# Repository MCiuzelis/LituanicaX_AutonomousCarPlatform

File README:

To activate the virtual env:
source ~/arducam_venv/bin/activate

hardware pwm:
sudo nano /boot/firmware/config.txt
dtoverlay=pwm-2chan,pin=12,func=4,pin2=18,func2=4

something similar for cam

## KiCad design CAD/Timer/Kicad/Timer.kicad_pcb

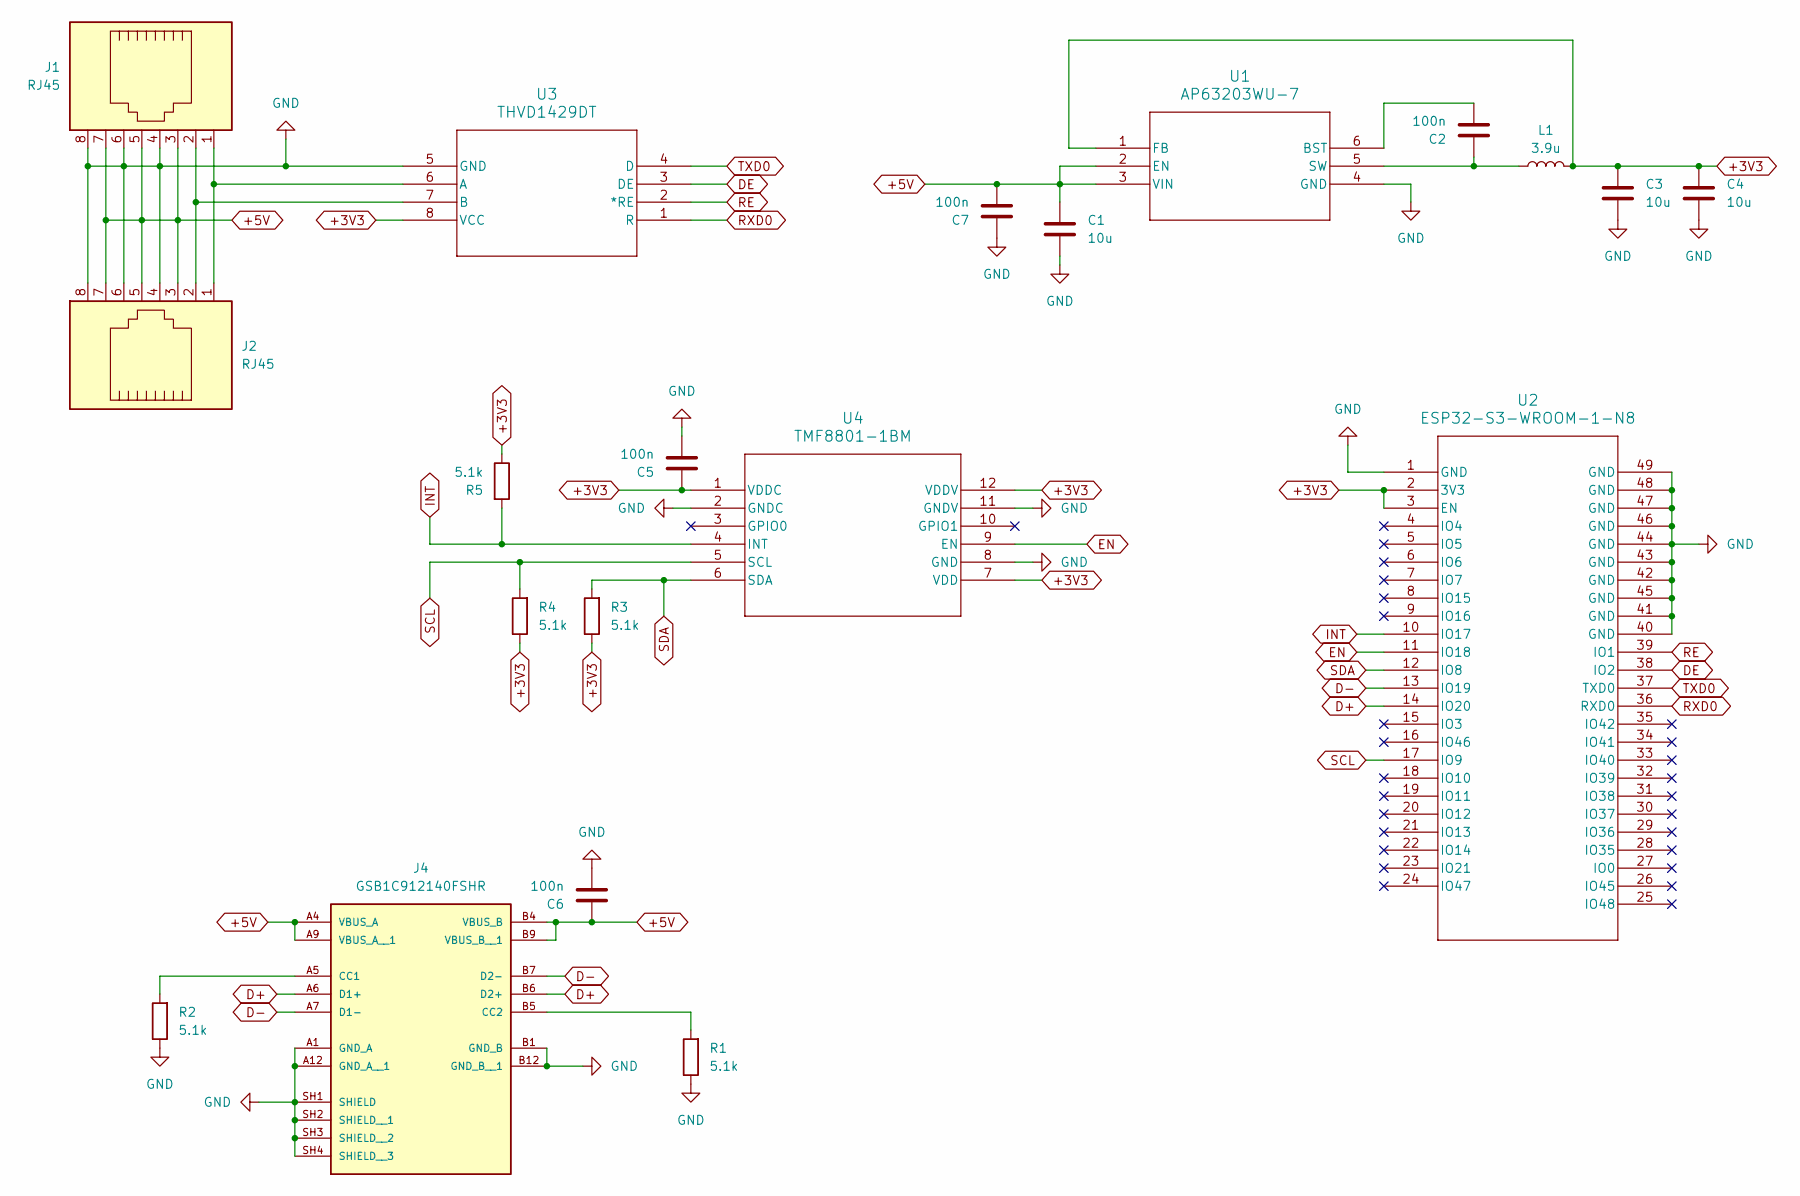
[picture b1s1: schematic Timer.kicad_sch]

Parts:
C1, C3, C4: 10u; C_1210_3225Metric_Pad1.33x2.70mm_HandSolder
C2, C5, C6, C7: 100n; C_0805_2012Metric_Pad1.18x1.45mm_HandSolder
J1, J2: RJ45; RJ45_Amphenol_RJHSE538X
J4: GSB1C912140FSHR; AMPHENOL_GSB1C912140FSHR; PARTREV AX1
L1: 3.9u; L_1210_3225Metric_Pad1.42x2.65mm_HandSolder
R1, R2, R3, R4, R5: 5.1k; R_0805_2012Metric_Pad1.20x1.40mm_HandSolder
U1: AP63203WU-7; AP63203WU-7_DIO
U2: ESP32-S3-WROOM-1-N8; ESP32-S3-WROOM-1_EXP
U3: THVD1429DT; D8_TEX
U4: TMF8801-1BM; TMF8801-1BM_AMS

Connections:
+3V3: C3.1, C4.1, C5.1, L1.2, R3.1, R4.1, R5.1, U1.1 (FB), U2.2 (3V3), U2.3 (EN), U3.8 (VCC), U4.1 (VDDC), U4.7 (VDD), U4.12 (VDDV)
+5V: C1.1, C6.1, C7.2, J1.3, J1.5, J1.7, J2.3, J2.5, J2.7, J4.A4 (VBUS_A), J4.A9 (VBUS_A__1), J4.B4 (VBUS_B), J4.B9 (VBUS_B__1), U1.2 (EN), U1.3 (VIN)
D+: J4.A6 (D1+), J4.B6 (D2+), U2.14 (IO20)
D-: J4.A7 (D1-), J4.B7 (D2-), U2.13 (IO19)
DE: U2.38 (IO2), U3.3 (DE)
EN: U2.11 (IO18), U4.9 (EN)
GND: C1.2, C3.2, C4.2, C5.2, C6.2, C7.1, J1.4, J1.6, J1.8, J2.4, J2.6, J2.8, J4.A1 (GND_A), J4.A12 (GND_A__1), J4.B1 (GND_B), J4.B12 (GND_B__1), J4.SH1 (SHIELD), J4.SH2 (SHIELD__1), J4.SH3 (SHIELD__2), J4.SH4 (SHIELD__3), R1.1, R2.1, U1.4 (GND), U2.1 (GND), U2.40 (GND), U2.41 (GND), U2.42 (GND), U2.43 (GND), U2.44 (GND), U2.45 (GND), U2.46 (GND), U2.47 (GND), U2.48 (GND), U2.49 (GND), U3.5 (GND), U4.2 (GNDC), U4.8 (GND), U4.11 (GNDV)
INT: R5.2, U2.10 (IO17), U4.4 (INT)
unnamed: J4.A5 (CC1), R2.2
unnamed: J4.B5 (CC2), R1.2
unnamed: C2.2, U1.6 (BST)
unnamed: C2.1, L1.1, U1.5 (SW)
unnamed: J1.1, J2.1, U3.6 (A)
unnamed: J1.2, J2.2, U3.7 (B)
RE: U2.39 (IO1), U3.2 (*RE)
RXD0: U2.36 (RXD0), U3.1 (R)
SCL: R4.2, U2.17 (IO9), U4.5 (SCL)
SDA: R3.2, U2.12 (IO8), U4.6 (SDA)
TXD0: U2.37 (TXD0), U3.4 (D)

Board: 2 copper layers, 20 parts (1 on the bottom side), 19 nets, no tracks yet.

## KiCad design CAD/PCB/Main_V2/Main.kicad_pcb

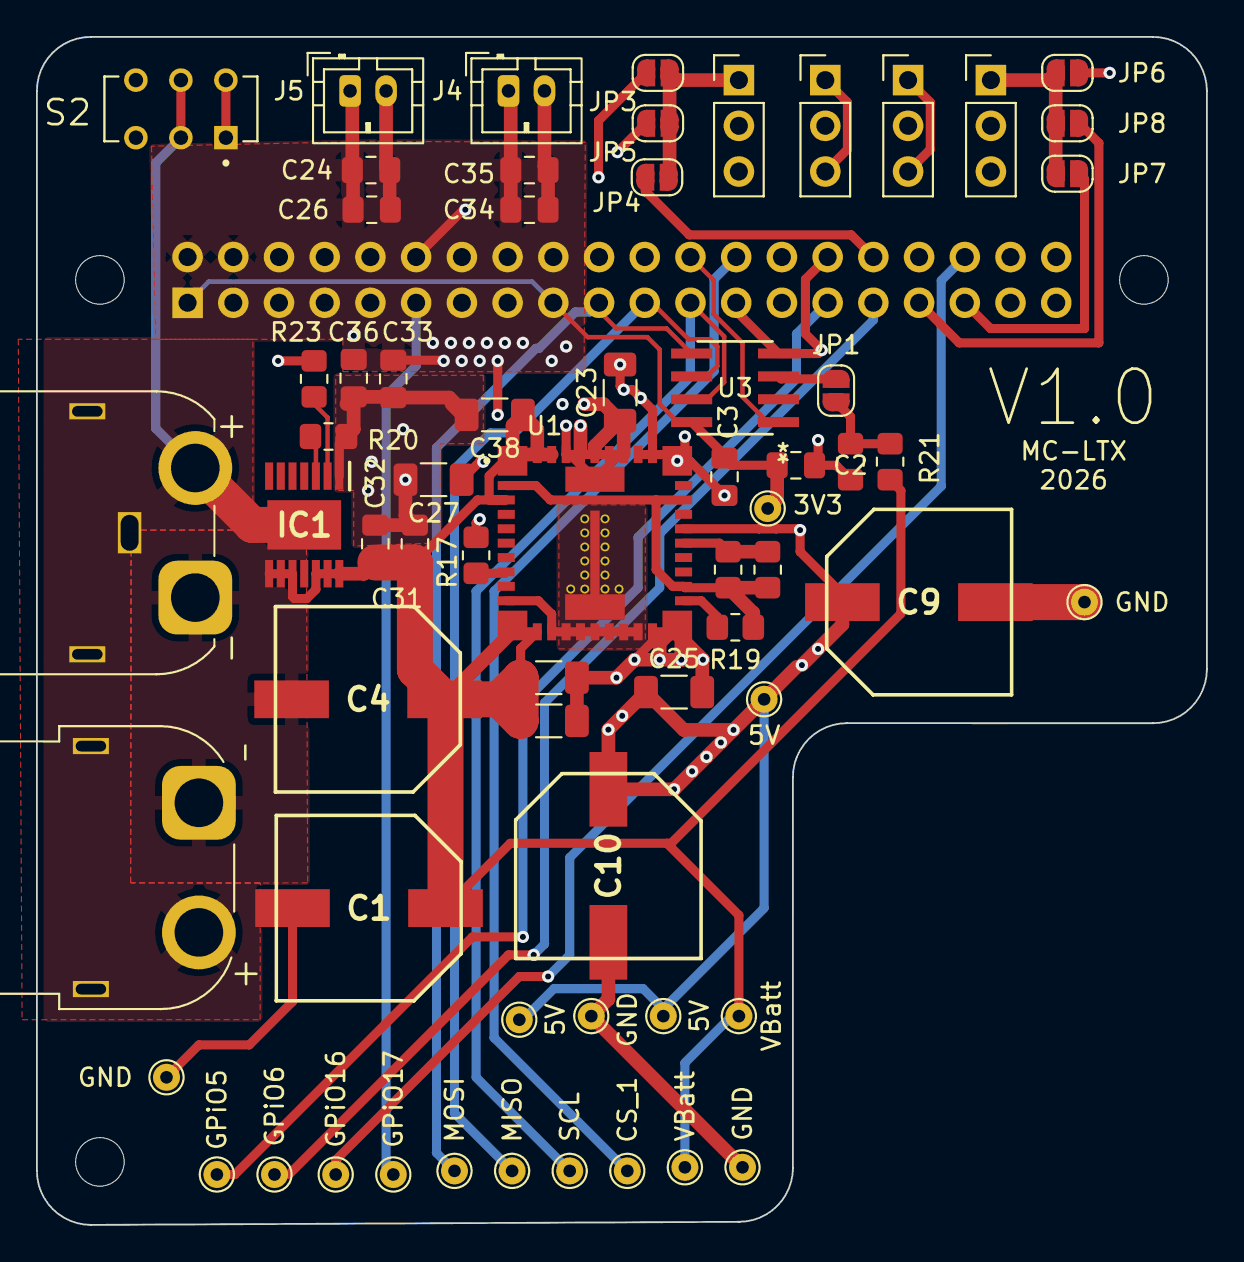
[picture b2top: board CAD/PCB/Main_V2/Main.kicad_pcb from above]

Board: 4 copper layers, 65.0 x 66.0 mm, 69 parts (1 on the bottom side), 33 nets.

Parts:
3V3: 3V3; TestPoint_THTPad_D1.5mm_Drill0.7mm
5V, 5V#2, 5V#3: GND; TestPoint_THTPad_D1.5mm_Drill0.7mm
C1, C4, C9, C10: APXG160ARA561MJ80G; CAPAE1030X820N
C2, C26, C32, C34, C36: 100nF; C_0805_2012Metric_Pad1.18x1.45mm_HandSolder
C3, C24, C31, C33, C35: 1uF; C_0805_2012Metric_Pad1.18x1.45mm_HandSolder
C23, C25, C27, C30, C37, C38: 22uF; C_1206_3216Metric_Pad1.33x1.80mm_HandSolder
CS_1: GND; TestPoint_THTPad_D1.5mm_Drill0.7mm
GND, GND3: GND; TestPoint_THTPad_D1.5mm_Drill0.7mm
GND#2, GND#3: GND; TestPoint_THTPad_D1.5mm_Drill0.7mm
GPiO5, GPiO6, GPiO16, GPiO17: GND; TestPoint_THTPad_D1.5mm_Drill0.7mm
IC1: BTS70021EPPXUMA1; SOP65P600X115-15N
J1: GPIO; PinSocket_2x20_P2.54mm_Vertical
J4, J5: CAM; JST_PH_B2B-PH-K_1x02_P2.00mm_Vertical
J8: XT60; AMASS_XT60IPW-M_1x03_P7.20mm_Horizontal
J9: XT60; AMASS_XT60PW-F_1x02_P7.20mm_Horizontal
JP1, JP3, JP4, JP5, JP6, JP7, JP8: SolderJumper_2_Open; SolderJumper-2_P1.3mm_Open_RoundedPad1.0x1.5mm
MH1, MH2, MH3: MountingHole_2.7mm_M2.5
MISO: GND; TestPoint_THTPad_D1.5mm_Drill0.7mm
MOSI: GND; TestPoint_THTPad_D1.5mm_Drill0.7mm
R17, R23: 10k; R_0805_2012Metric_Pad1.20x1.40mm_HandSolder
R18: 200; R_0805_2012Metric_Pad1.20x1.40mm_HandSolder
R19: 68k; R_0805_2012Metric_Pad1.20x1.40mm_HandSolder
R20, R22, R24: 4.7k; R_0805_2012Metric_Pad1.20x1.40mm_HandSolder
R21: 15k; R_0805_2012Metric_Pad1.20x1.40mm_HandSolder
S2: EG1271; SW_EG1271
SCL: GND; TestPoint_THTPad_D1.5mm_Drill0.7mm
SERVO3: Conn_01x03; PinHeader_1x03_P2.54mm_Vertical
Servo1: GPIO23; PinHeader_1x03_P2.54mm_Vertical
Servo2: GPIO24; PinHeader_1x03_P2.54mm_Vertical
THROTTLE1: Conn_01x03; PinHeader_1x03_P2.54mm_Vertical
U1: LMZ31707RVQR; CONV_LMZ31707RVQR
U3: MCP3202T-CI/SN; SOIC8-N_MC_MCH-M
VBatt: VBATT; TestPoint_THTPad_D1.5mm_Drill0.7mm
VBatt#2: GND; TestPoint_THTPad_D1.5mm_Drill0.7mm

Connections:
+3V3: 3V3.1 (1_1), C2.1, C3.1, J1.1, J1.17, U3.8 (VDD/VREF)
+5V: 5V.1 (1_1), 5V#2.1 (1_1), 5V#3.1 (1_1), C9.2 (-), C10.2 (-), C23.1, C24.1, C25.1, C26.1, C27.1, C33.2, C34.2, C35.2, C36.2, J1.2, J1.4, J4.1, J5.1, R17.2, SERVO3.2, U1.27 (SENSE+), U1.34 (VOUT_34), U1.35 (VOUT_35), U1.36 (VOUT_36), U1.37 (VOUT_37), U1.38 (VOUT_38), U1.41 (VOUT_41)
/GPIO5: GPiO5.1 (1_1), J1.29
/GPIO6: GPiO6.1 (1_1), J1.31
/GPIO12/PWM0: J1.32, JP5.1 (A)
/GPIO13/PWM1: J1.33, JP8.2 (B)
/GPIO14/TXD0: J1.8, JP4.2 (B)
/GPIO15/RXD0: J1.10, JP3.1 (A)
/GPIO16: GPiO16.1 (1_1), J1.36
/GPIO17: GPiO17.1 (1_1), J1.11
/GPIO18/PCM.CLK: J1.12, JP6.1 (A)
/GPIO19/PCM.FS: J1.35, JP7.2 (B)
/GPIO23: J1.16, Servo1.1, Servo1.3
/GPIO24: J1.18, Servo2.1, Servo2.3
AGND: R18.1, R19.2, R24.1, U1.2 (AGND_2), U1.23 (AGND_23), U1.29 (STSEL)
Analog_In_1: JP1.2 (B), U3.3 (CH1)
CS_0: J1.24, U3.1 (*CS/SHDN)
CS_1: CS_1.1 (1_1), J1.26
GND: C1.1 (+), C2.2, C3.2, C4.1 (+), C9.1 (+), C10.1 (+), C23.2, C24.2, C25.2, C26.2, C27.2, C30.2, C31.2, C32.2, C33.1, C34.1, C35.1, C36.1, C37.2, C38.2, GND.1 (1_1), GND3.1 (1_1), GND#2.1 (1_1), GND#3.1 (1_1), IC1.1 (GND), J1.6, J1.9, J1.14, J1.20, J1.25, J1.30, J1.34, J1.39, J4.2, J5.2, J8.1, J9.1, R20.2, R22.1, SERVO3.3, THROTTLE1.3, U1.20 (PGND_20), U1.21 (PGND_21), U1.31 (PGND_31), U1.32 (PGND_32), U1.33 (PGND_33), U3.4 (VSS)
MISO: J1.21, MISO.1 (1_1), U3.6 (DOUT)
MOSI: J1.19, MOSI.1 (1_1), U3.5 (DIN)
unnamed: IC1.3 (DEN), R20.1
unnamed: IC1.2 (IN), R23.2
unnamed: IC1.15 (VS), J8.2, J9.2, S2.2, S2.5
unnamed: JP1.1 (A), R21.1, R22.2
unnamed: R23.1, S2.1, S2.4
unnamed: R17.1, U1.8 (PWRGD)
unnamed: R19.1, U1.22 (RT/CLK)
unnamed: R18.2, R24.2, U1.26 (VADJ)
PWM_0: JP3.2 (B), JP4.1 (A), JP5.2 (B), SERVO3.1
PWM_1: JP6.2 (B), JP7.1 (A), JP8.1 (A), THROTTLE1.1
SCL: J1.23, SCL.1 (1_1), U3.7 (CLK)
VBatt: C1.2 (-), C4.2 (-), C30.1, C31.1, C32.1, C37.1, C38.1, IC1.8 (OUT_1), IC1.9 (OUT_2), IC1.10 (OUT_3), IC1.12 (OUT_4), IC1.13 (OUT_5), IC1.14 (OUT_6), R21.2, U1.1 (PVIN_1), U1.3 (VIN), U1.11 (PVIN_11), U1.12 (PVIN_12), U1.39 (PVIN_39), U1.40 (PVIN_40), VBatt.1 (1_1), VBatt#2.1 (1_1)

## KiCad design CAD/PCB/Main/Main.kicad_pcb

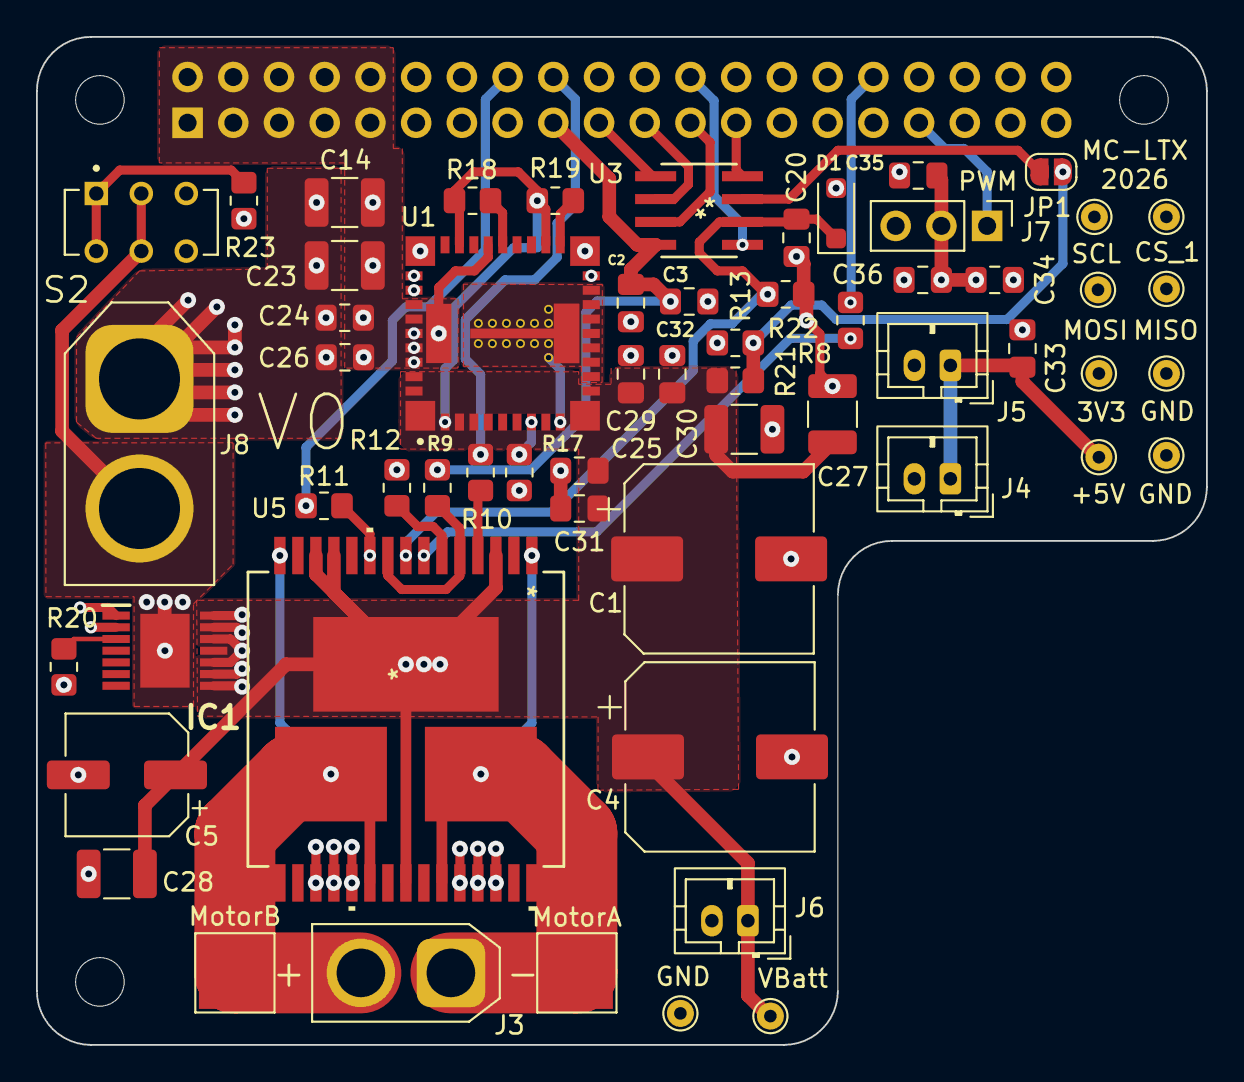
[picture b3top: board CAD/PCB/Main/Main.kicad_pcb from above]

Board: 4 copper layers, 65.0 x 56.0 mm, 63 parts (1 on the bottom side), 31 nets.

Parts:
3V3: GND; TestPoint_THTPad_D1.5mm_Drill0.7mm
+5V: GND; TestPoint_THTPad_D1.5mm_Drill0.7mm
C1, C4: C_Polarized; CP_Elec_10x10
C2, C20, C26, C29, C32, C34, C36: 100nF; C_0805_2012Metric_Pad1.18x1.45mm_HandSolder
C3, C24, C25, C31, C33, C35: 1uF; C_0805_2012Metric_Pad1.18x1.45mm_HandSolder
C5: C_Polarized; CP_Elec_6.3x7.7
C14, C27, C28: 47uF; C_1210_3225Metric_Pad1.33x2.70mm_HandSolder
C23, C30: 22uF; C_1210_3225Metric_Pad1.33x2.70mm_HandSolder
CS_1: GND; TestPoint_THTPad_D1.5mm_Drill0.7mm
D1: D_Zener_Filled; D_SOD-123F
GND: GND; TestPoint_THTPad_D1.5mm_Drill0.7mm
GND#2, GND#3: GND; TestPoint_THTPad_D1.5mm_Drill0.7mm
IC1: BTS70021EPPXUMA1; SOP65P600X115-15N
J1: GPIO; PinSocket_2x20_P2.54mm_Vertical
J3: XT30; AMASS_XT30U-M_1x02_P5.0mm_Vertical
J4, J5, J6: JST_PH; JST_PH_B2B-PH-K_1x02_P2.00mm_Vertical
J7: Conn_01x03; PinHeader_1x03_P2.54mm_Vertical
J8: XT60; AMASS_XT60-M_1x02_P7.20mm_Vertical
JP1: SolderJumper_2_Open; SolderJumper-2_P1.3mm_Open_RoundedPad1.0x1.5mm
MH1, MH2, MH3: MountingHole_2.7mm_M2.5
MISO: GND; TestPoint_THTPad_D1.5mm_Drill0.7mm
MOSI: GND; TestPoint_THTPad_D1.5mm_Drill0.7mm
MotorA: MotorOutA; TestPoint_Pad_4.0x4.0mm
MotorB: MotorOutB; TestPoint_Pad_4.0x4.0mm
R8, R9, R10, R11: 1k; R_0805_2012Metric_Pad1.20x1.40mm_HandSolder
R12, R17, R23: 10k; R_0805_2012Metric_Pad1.20x1.40mm_HandSolder
R13: 1.5k; R_0805_2012Metric_Pad1.20x1.40mm_HandSolder
R18: 185; R_0805_2012Metric_Pad1.20x1.40mm_HandSolder
R19: 63.4k; R_0805_2012Metric_Pad1.20x1.40mm_HandSolder
R20: 4.7k; R_0805_2012Metric_Pad1.20x1.40mm_HandSolder
R21: 94k; R_0805_2012Metric_Pad1.20x1.40mm_HandSolder
R22: 35k; R_0805_2012Metric_Pad1.20x1.40mm_HandSolder
S2: EG1271; SW_EG1271
SCL: GND; TestPoint_THTPad_D1.5mm_Drill0.7mm
U1: LMZ31707RVQR; CONV_LMZ31707RVQR
U3: MCP3202T-CI/SN; SOIC8-N_MC_MCH-M
U5: VNH5019ATR-E; MultiPowerSO-30_STM-M
VBatt: GND; TestPoint_THTPad_D1.5mm_Drill0.7mm

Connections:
+3V3: 3V3.1 (1_1), C2.1, C3.1, J1.1, J1.17, R9.2, U3.8 (VDD/VREF)
+5V: +5V.1 (1_1), C14.1, C23.1, C24.1, C26.1, C33.2, C34.2, C35.2, C36.2, J1.2, J1.4, J4.1, J5.1, J7.2, R17.2, U1.27 (SENSE+), U1.34 (VOUT_34), U1.35 (VOUT_35), U1.36 (VOUT_36), U1.37 (VOUT_37), U1.38 (VOUT_38), U1.41 (VOUT_41)
AGND: R18.1, R19.2, U1.2 (AGND_2), U1.23 (AGND_23), U1.29 (STSEL)
Analog_In_0: C20.2, D1.1 (K), R13.2, U3.2 (CH0), U5.8 (CS)
Analog_In_1: JP1.2 (B), U3.3 (CH1)
CS_0: J1.24, U3.1 (*CS/SHDN)
CS_1: CS_1.1 (1_1), J1.26
Dir_1: J1.18, R10.2
Dir_2: J1.16, R11.1
GND: C1.2, C2.2, C3.2, C4.2, C5.2, C14.2, C20.1, C23.2, C24.2, C25.1, C26.2, C27.2, C28.2, C29.1, C30.2, C31.2, C32.2, C33.1, C34.1, C35.1, C36.1, D1.2 (A), GND.1 (1_1), GND#2.1 (1_1), GND#3.1 (1_1), IC1.1 (GND), J1.6, J1.9, J1.14, J1.20, J1.25, J1.30, J1.34, J1.39, J4.2, J5.2, J6.2, J7.3, J8.1, R12.2, R13.1, R20.2, R22.1, U1.20 (PGND_20), U1.21 (PGND_21), U1.31 (PGND_31), U1.32 (PGND_32), U1.33 (PGND_33), U3.4 (VSS), U5.18 (GNDB), U5.19 (GNDB), U5.20 (GNDB), U5.26 (GNDA), U5.27 (GNDA), U5.28 (GNDA)
MISO: J1.21, MISO.1 (1_1), U3.6 (DOUT)
MOSI: J1.19, MOSI.1 (1_1), U3.5 (DIN)
MotorOutA: J3.1, MotorA.1 (1_1), U5.1 (OUTA), U5.25 (OUTA), U5.30 (OUTA), U5.32 (OUTA)
MotorOutB: J3.2, MotorB.1 (1_1), U5.15 (OUTB), U5.16 (OUTB), U5.21 (OUTB), U5.33 (OUTB)
unnamed: IC1.3 (DEN), R20.1
unnamed: IC1.2 (IN), R23.2
unnamed: IC1.15 (VS), J8.2, S2.2, S2.5
unnamed: JP1.1 (A), R21.1, R22.2
unnamed: R23.1, S2.1, S2.4
unnamed: R17.1, U1.8 (PWRGD)
unnamed: R19.1, U1.22 (RT/CLK)
unnamed: R18.2, U1.26 (VADJ)
unnamed: R12.1, U5.6 (CS_DIS)
unnamed: R9.1, U5.5 (ENA/DIAGA), U5.9 (ENB/DIAGB)
unnamed: R10.1, U5.4 (INA)
unnamed: R11.2, U5.10 (INB)
unnamed: R8.1, U5.7 (PWM)
PWM_0: J1.32, R8.2
PWM_1: J1.33, J7.1
SCL: J1.23, SCL.1 (1_1), U3.7 (CLK)
VBatt: C1.1, C4.1, C5.1, C25.2, C27.1, C28.1, C29.2, C30.1, C31.1, C32.1, IC1.8 (OUT_1), IC1.9 (OUT_2), IC1.10 (OUT_3), IC1.12 (OUT_4), IC1.13 (OUT_5), IC1.14 (OUT_6), J6.1, R21.2, U1.1 (PVIN_1), U1.3 (VIN), U1.11 (PVIN_11), U1.12 (PVIN_12), U1.39 (PVIN_39), U1.40 (PVIN_40), U5.3 (VCC), U5.12 (VBAT), U5.13 (VCC), U5.23 (VCC), U5.31 (VCC), VBatt.1 (1_1)

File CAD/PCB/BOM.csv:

"Reference","Value","Datasheet","Footprint","Qty","DNP"
"5V1,CS_1,GND1,GND2,GND3,MISO1,MOSI1,SCL1,TP12,VBatt1","GND","","TestPoint:TestPoint_THTPad_D1.5mm_Drill0.7mm","10",""
"C1,C4,C5","C_Polarized","","Capacitor_SMD:CP_Elec_10x10,Capacitor_SMD:CP_Elec_6.3x7.7","3",""
"C2,C20,C26,C29,C32,C34,C36","100nF","","Capacitor_SMD:C_0805_2012Metric_Pad1.18x1.45mm_HandSolder","7",""
"C3,C24,C25,C31,C33,C35","1uF","","Capacitor_SMD:C_0805_2012Metric_Pad1.18x1.45mm_HandSolder","6",""
"C14,C27,C28","47uF","","Capacitor_SMD:C_1210_3225Metric_Pad1.33x2.70mm_HandSolder","3",""
"C23,C30","22uF","","Capacitor_SMD:C_1210_3225Metric_Pad1.33x2.70mm_HandSolder","2",""
"D1","D_Zener_Filled","","Diode_SMD:D_SOD-123F","1",""
"IC1","BTS70021EPPXUMA1","https://datasheet.datasheetarchive.com/originals/distributor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","RC_CAR:SOP65P600X115-15N","1",""
"J1","GPIO","","Connector_PinSocket_2.54mm:PinSocket_2x20_P2.54mm_Vertical","1",""
"J3","XT30","","Connector_AMASS:AMASS_XT30U-M_1x02_P5.0mm_Vertical","1",""
"J4,J5,J6","JST_PH","","Connector_JST:JST_PH_B2B-PH-K_1x02_P2.00mm_Vertical","3",""
"J7","Conn_01x03","","Connector_PinHeader_2.54mm:PinHeader_1x03_P2.54mm_Vertical","1",""
"J8","XT60","","Connector_AMASS:AMASS_XT60-M_1x02_P7.20mm_Vertical","1",""
"MotorA1","MotorOutA","","TestPoint:TestPoint_Pad_4.0x4.0mm","1",""
"MotorB1","MotorOutB","","TestPoint:TestPoint_Pad_4.0x4.0mm","1",""
"R8,R9,R10,R11","1k","","Resistor_SMD:R_0805_2012Metric_Pad1.20x1.40mm_HandSolder","4",""
"R12,R17,R23","10k","","Resistor_SMD:R_0805_2012Metric_Pad1.20x1.40mm_HandSolder","3",""
"R13","1.5k","","Resistor_SMD:R_0805_2012Metric_Pad1.20x1.40mm_HandSolder","1",""
"R18","185","","Resistor_SMD:R_0805_2012Metric_Pad1.20x1.40mm_HandSolder","1",""
"R19","63.4k","","Resistor_SMD:R_0805_2012Metric_Pad1.20x1.40mm_HandSolder","1",""
"R20","4.7k","","Resistor_SMD:R_0805_2012Metric_Pad1.20x1.40mm_HandSolder","1",""
"R21","94k","","Resistor_SMD:R_0805_2012Metric_Pad1.20x1.40mm_HandSolder","1",""
"R22","35k","","Resistor_SMD:R_0805_2012Metric_Pad1.20x1.40mm_HandSolder","1",""
"S2","EG1271","","RC_CAR:SW_EG1271","1",""
"U1","LMZ31707RVQR","","RC_CAR:CONV_LMZ31707RVQR","1",""
"U3","MCP3202T-CI/SN","MCP3202T-CI/SN","RC_CAR:SOIC8-N_MC_MCH-M","1",""
"U5","VNH5019ATR-E","https://www.st.com/resource/en/datasheet/vnh5019a-e.pdf","RC_CAR:MultiPowerSO-30_STM-M","1",""

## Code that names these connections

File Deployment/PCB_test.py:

import time
import math
import spidev
import RPi.GPIO as GPIO
from hardwarepwm import HardwarePWM # Source 1

# --- PIN CONFIGURATION ---
PIN_DIR_1 = 24  # INA
PIN_DIR_2 = 23  # INB
ADC_CS_PIN = 8  # SPI CE0
SERVO_PWM_CHAN = 1 # PWM_1 (GPIO13)
MOTOR_PWM_CHAN = 0 # PWM_0 (GPIO12)

# --- CONSTANTS ---
V_REF = 3.3      # RP5 Logic Voltage
K_RATIO = 7000   # Typical VNH5019 Current Sense Ratio
R_SENSE = 1500   # 1.5k Ohm resistor on CS pin

# --- INITIALIZATION ---
GPIO.setmode(GPIO.BCM)
GPIO.setup(PIN_DIR_1, GPIO.OUT)
GPIO.setup(PIN_DIR_2, GPIO.OUT)

# SPI for MCP3202
spi = spidev.SpiDev()
spi.open(0, 0) # Bus 0, Device 0 (GPIO8)
spi.max_speed_hz = 1000000 # 1MHz

# Hardware PWM Setup
# Motor: 20kHz to avoid audible noise
motor_pwm = HardwarePWM(pwm_channel=MOTOR_PWM_CHAN, hz=20000)
motor_pwm.start(0)

# Servo: 50Hz standard
servo_pwm = HardwarePWM(pwm_channel=SERVO_PWM_CHAN, hz=50)
servo_pwm.start(7.5) # Neutral (1.5ms)

def read_motor_current():
    """
    Reads MCP3202 CH0 and calculates motor current in Amps.
    Command: Start(1), SGL(1), CH0(0), MSBF(1) -> 0xA0
    """
    #
    reply = spi.xfer2([0x01, 0xA0, 0x00])
    # Extract 12 bits from the 3-byte response
    adc_raw = ((reply[1] & 0x0F) << 8) + reply[2]
    
    # Calculate Voltage
    v_sense = (adc_raw / 4095.0) * V_REF
    
    # Calculate Motor Current: I_out = (V_sense / R_sense) * K
    i_out = (v_sense / R_SENSE) * K_RATIO
    return i_out

try:
    print("Starting Sine Sweep... Press Ctrl+C to stop.")
    start_time = time.time()
    
    while True:
        t = time.time() - start_time
        
        # 1. Servo Sine Sweep (Range: 5% to 10% duty cycle)
        # Using a 0.5Hz frequency for the sweep
        servo_duty = 7.5 + 2.5 * math.sin(2 * math.pi * 0.5 * t)
        servo_pwm.change_duty_cycle(servo_duty)
        
        # 2. Motor Sine Sweep (Range: -100% to 100% speed)
        motor_val = math.sin(2 * math.pi * 0.2 * t) # 0.2Hz sweep
        
        if motor_val >= 0:
            GPIO.output(PIN_DIR_1, GPIO.HIGH) # INA=1
            GPIO.output(PIN_DIR_2, GPIO.LOW)  # INB=0 (CW)
            duty = motor_val * 100
        else:
            GPIO.output(PIN_DIR_1, GPIO.LOW)  # INA=0
            GPIO.output(PIN_DIR_2, GPIO.HIGH) # INB=1 (CCW)
            duty = abs(motor_val) * 100
            
        motor_pwm.change_duty_cycle(duty)
        
        # 3. Read and Print Current
        current = read_motor_current()
        print(f"Time: {t:.2f}s | Servo Duty: {servo_duty:.1f}% | Motor: {motor_val*100:.1f}% | Amps: {current:.3f}A")
        
        time.sleep(0.05)

except KeyboardInterrupt:
    print("\nStopping...")
finally:
    motor_pwm.stop()
    servo_pwm.stop()
    GPIO.cleanup()
    spi.close()

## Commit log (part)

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2026-02-22 first commit, basic training working
2026-02-25 traffic cone sim working
2026-03-05 rc car working
2026-03-12 temp 1
2026-03-12 REVERTED, STILL FIGHTING RAMPS
2026-03-13 colider finally fixed
2026-03-14 backup
2026-03-14 vm test
2026-03-14 script
2026-03-15 ready for ai
2026-03-16 RAMPS ARE FINALLY WORKING
2026-03-24 5m/s still can't complete a lap
2026-03-26 depth cam + lidar
2026-04-12 tained a pretty good model, ready for irl testing
2026-04-13 slow car retrain
2026-04-16 car finally working
2026-04-16 put all in one repo
2026-04-16 refractored code in new repo runs, updated to hardware pwm
2026-04-17 add pcb components
2026-04-17 fixed blender track scale and general blender cleanup
2026-04-17 refractored training, remove redundanct code, add readme and gitignore, fixed blender imports and noise in visualize
2026-04-19 Initial design
2026-04-20 PCB almost done
2026-04-21 pcb order is in
2026-04-26 move to uv from conda, added single dependancy install script under training/install.sh
2026-04-26 Remove .DS_Store files
2026-04-26 Remove tracked .DS_Store files
2026-04-26 CAD track setup
2026-04-26 update readme, kubuntu 24.04 LTS finally working with uv
2026-04-28 add blender files, fixed usdf imports into isaac sim, added zero power behavior brake
2026-04-29 trying runpod again
2026-04-29 rez just for runpod
2026-05-06 pcb tested, all works, move to uv venv on deployment board
2026-05-08 add ros 2 jazzy, fix pwm
2026-05-09 Ros2 dashboard working, rosboard added, camera working state unknown
2026-05-14 more ros improvements, better node separation, separate html
2026-05-14 untrack files, fix secret
2026-05-14 encoder working
2026-05-18 solidworks pcb enclosure
2026-05-22 training changes
2026-05-22 Revert "Merge pull request #8 from MCiuzelis/training_again"
    This reverts commit 45457efedb9c133d4c12ec96618f12a739c6362b, reversing
    changes made to 56e53ccec39eb78b8de2ab486bb5814608f913b9.
2026-05-22 training fix
2026-05-22 docker
2026-05-23 container pyproject.toml
2026-05-23 tensorboard fix
2026-05-29 fix ros, both cameras and hardware pwm working
2026-05-30 fix training code, document driver compatbility
2026-06-02 integration hell, servo 50hz software pwm, motor 20khz hardware pwm
2026-06-04 before claude changes
2026-06-04 more clauder_)
2026-06-07 more changes
2026-06-07 add velocity and distance telemetry
2026-06-08 acceleration test, tuned physics
2026-06-08 scale 0.755
2026-06-08 acceleration ros test
2026-06-08 optimization, cpu usage still high
2026-06-11 training gives me hope
2026-06-13 hopefully training good enough
2026-06-13 update deployment
2026-06-13 gemini optimization
2026-06-14 almost working
2026-06-14 can do 3 laps
2026-06-14 final training before premier
2026-06-15 ready for training, out of vram
2026-06-15 training
2026-06-23 scale larger
2026-06-23 vram usage still high
2026-06-23 still not working in play
2026-06-24 lane extraction
2026-06-24 garbage
2026-06-25 try CNN with MLP on depth cams
2026-06-25 blender
